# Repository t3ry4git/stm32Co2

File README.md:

# stm32Co2

A simple CO2 and environmental monitor based on the STM32F103C8 microcontroller. The firmware reads temperature and humidity from a DHT22 sensor, measures CO2 concentration using an MHZ19B module and displays values on an SSD1306 OLED screen.

## Hardware requirements

- **MCU:** STM32F103C8 ("Blue Pill" or compatible)
- **Temperature/Humidity sensor:** DHT22
- **CO2 sensor:** MHZ19B (UART interface)
- **Display:** SSD1306 I2C OLED

## Building with STM32CubeIDE

1. Open the `test.ioc` project file in STM32CubeIDE.
2. Let CubeIDE generate the project files if prompted.
3. Build the `test` target from the IDE. Default settings produce both `Debug` and `Release` outputs.
4. Flash the resulting binary to your board using the built‑in CubeIDE programmer or an external tool such as ST‑Link.

## Third‑party software

This repository includes STM32 HAL drivers from STMicroelectronics under the BSD‑3‑Clause license as found in `Drivers/STM32F1xx_HAL_Driver/LICENSE.txt`. The SSD1306 display driver and font code in `Core/Src` and `Core/Inc` are distributed under the GNU GPL version 3.

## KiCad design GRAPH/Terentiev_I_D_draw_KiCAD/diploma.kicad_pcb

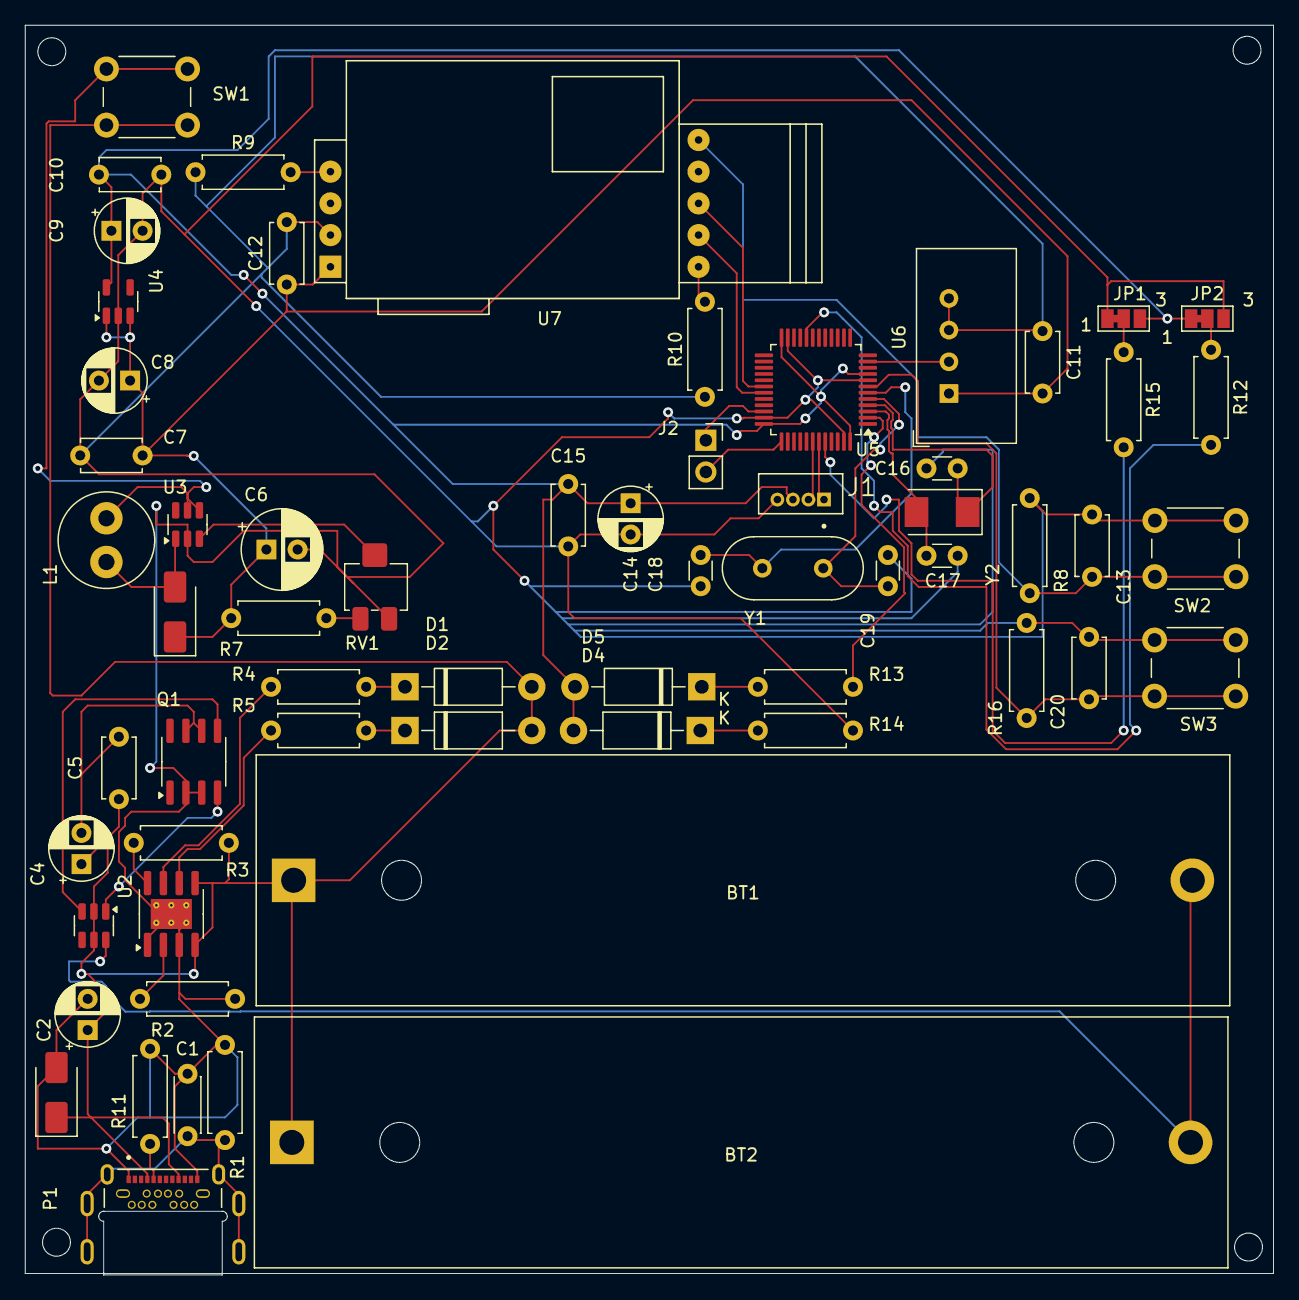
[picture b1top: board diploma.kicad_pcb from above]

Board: 2 copper layers, 100.0 x 100.0 mm, 62 parts (0 on the bottom side), 42 nets.

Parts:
BT1, BT2: 1043; BatteryHolder_MPD_BH-18650-PC2
C1: 1 nF; C_Disc_D4.3mm_W1.9mm_P5.00mm
C2, C4, C8, C9, C14: 10 uF; CP_Radial_D5.0mm_P2.50mm
C5, C7, C10, C11, C12, C13, C15, C20: 100 nF; C_Disc_D4.7mm_W2.5mm_P5.00mm
C6: 22 uF; CP_Radial_D6.3mm_P2.50mm
C16, C17: 100 pF; C_Disc_D3.0mm_W1.6mm_P2.50mm
C18, C19: 12 pF; C_Disc_D3.0mm_W1.6mm_P2.50mm
D1: RED; D_DO-41_SOD81_P10.16mm_Horizontal
D2, D4, D5: GREEN; D_DO-41_SOD81_P10.16mm_Horizontal
D3, D6: SS34; D_SMA
J1: OLED_LCD; TE_1734598-4
J2: Flash; PinSocket_1x02_P2.54mm_Vertical
JP1: Boot0; SolderJumper-3_P1.3mm_Bridged12_Pad1.0x1.5mm_NumberLabels
JP2: Boot1; SolderJumper-3_P1.3mm_Bridged12_Pad1.0x1.5mm_NumberLabels
L1: 22uH/2A; L_Radial_D7.5mm_P3.50mm_Fastron_07P
P1: USBC; usbc
Q1: FS8205A; SOIC-8_3.9x4.9mm_P1.27mm
R1: 1 M; R_Axial_DIN0207_L6.3mm_D2.5mm_P7.62mm_Horizontal
R2: 1.2k; R_Axial_DIN0207_L6.3mm_D2.5mm_P7.62mm_Horizontal
R3, R8, R16: 10 k; R_Axial_DIN0207_L6.3mm_D2.5mm_P7.62mm_Horizontal
R4, R5: 1k; R_Axial_DIN0207_L6.3mm_D2.5mm_P7.62mm_Horizontal
R7, R9, R10: 100 k; R_Axial_DIN0207_L6.3mm_D2.5mm_P7.62mm_Horizontal
R11: 5.1 k; R_Axial_DIN0207_L6.3mm_D2.5mm_P7.62mm_Horizontal
R12, R15: 100k; R_Axial_DIN0207_L6.3mm_D2.5mm_P7.62mm_Horizontal
R13, R14: 510; R_Axial_DIN0207_L6.3mm_D2.5mm_P7.62mm_Horizontal
RV1: 2.2 k; Potentiometer_Bourns_3214X_Vertical
SW1: Enable Switch; SW_PUSH_6mm
SW2: Calibrate; SW_PUSH_6mm
SW3: Reset; SW_PUSH_6mm
U1: TP4056; SOIC-8-1EP_3.9x4.9mm_P1.27mm_EP2.41x3.3mm_ThermalVias
U2: DW01A; SOT-23-6
U3: MT3608; SOT-23-6
U4: AP2112K-3.3; SOT-23-5
U5: STM32F103C8T6; LQFP-48_7x7mm_P0.5mm
U6: DHT22; ASAIR_AM2302_P2.54mm_Vertical
U7: MH-Z19B
Y1: 8MHz; Crystal_HC49-U_Vertical
Y2: 32768Hz; Crystal_SMD_Abracon_ABM3-2Pin_5.0x3.2mm

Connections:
+3.3V: C9.1, C10.1, C14.1, C15.1, D4.2 (A), D5.2 (A), J1.3, JP1.3 (B), JP2.1 (A), U4.5 (VOUT), U5.9 (VDDA), U5.24 (VDD), U5.36 (VDD), U5.48 (VDD)
+5V: C6.1, C7.1, C8.1, C11.2, C12.1, D3.1 (K), R7.1, U4.1 (VIN), U4.3 (EN), U6.1 (VDD), U7.VIN
GND: C1.2, C2.2, C6.2, C7.2, C8.2, C9.2, C10.2, C11.1, C12.2, C13.2, C14.2, C15.2, C16.1, C17.1, C18.2, C19.2, C20.2, D6.2 (A), J1.4, JP1.1 (A), JP2.3 (B), P1.A1 (GND_A), P1.A12 (GND_A), Q1.2, Q1.3, R1.2, R2.2, R8.2, R9.1, R10.1, R11.2, R14.1, R16.1, RV1.3, SW2.2, SW3.2, U1.1 (TEMP), U1.3 (GND), U1.9 (EPAD), U3.2 (GND), U4.2 (GND), U5.8 (VSSA), U5.23 (VSS), U5.35 (VSS), U5.47 (VSS), U6.3 (GND), U6.4 (GND), U7.GND
unnamed: C1.1, P1.SH1 (SHIELD), P1.SH2 (SHIELD), P1.SH3 (SHIELD), P1.SH4 (SHIELD), P1.SH5 (SHIELD), P1.SH6 (SHIELD), R1.1
unnamed: C4.2, C5.2, Q1.6, Q1.7
unnamed: C13.1, R8.1, SW2.1, U7.HD
unnamed: BT1.1, BT2.1, C2.1, C4.1, C5.1, D1.2 (A), D2.2 (A), D6.1 (K), P1.A4 (VBUS_A), P1.A9 (VBUS_A), R3.1, SW1.1 (A), U1.4 (V_{CC}), U1.5 (BAT), U2.2 (CS), U2.5 (VCC)
unnamed: D1.1 (K), R4.1
unnamed: D2.1 (K), R5.2
unnamed: D3.2 (A), L1.2, U3.1 (SW)
unnamed: D4.1 (K), R14.2
unnamed: D5.1 (K), R13.2
unnamed: J1.1, U5.43 (PB7)
unnamed: J1.2, U5.42 (PB6)
unnamed: J2.1, U5.34 (PA13)
unnamed: J2.2, U5.37 (PA14)
unnamed: JP1.2 (C), R15.1
unnamed: JP2.2 (C), R12.1
unnamed: P1.A5 (CC1), R11.1
unnamed: R7.2, RV1.1
unnamed: R9.2, U7.PWM
unnamed: R10.2, U7.VO
unnamed: L1.1, SW1.2 (B), U3.4 (EN), U3.5 (IN)
unnamed: R3.2, U1.8 (CE)
unnamed: R2.1, U1.2 (PROG)
unnamed: R4.2, U1.7 (~CHRG)
unnamed: R5.1, U1.6 (~STDBY)
unnamed: BT1.2, BT2.2, U2.6 (GND)
unnamed: Q1.5, U2.3 (OC)
unnamed: Q1.4, U2.1 (OD)
unnamed: RV1.2, U3.3 (FB)
unnamed: R15.2, U5.44 (BOOT0)
unnamed: C20.1, R16.2, SW3.1, U5.7 (NRST)
unnamed: U5.11 (PA1), U6.2 (SDA)
unnamed: U5.30 (PA9), U7.TX
unnamed: U5.31 (PA10), U7.RX
unnamed: R12.2, U5.20 (PB2)
unnamed: R13.1, U5.2 (PC13)
unnamed: C17.2, U5.3 (PC14), Y2.2
unnamed: C16.2, U5.4 (PC15), Y2.1
unnamed: C19.1, U5.5 (PD0), Y1.2
unnamed: C18.1, U5.6 (PD1), Y1.1

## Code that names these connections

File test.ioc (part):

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Mcu.Name=STM32F103C(8-B)Tx
Mcu.Package=LQFP48
Mcu.UserName=STM32F103C8Tx
PA10.Mode=Asynchronous
PA10.Signal=USART1_RX
PA13.Mode=Serial_Wire
PA13.Signal=SYS_JTMS-SWDIO
PA14.Mode=Serial_Wire
PA14.Signal=SYS_JTCK-SWCLK
PA9.Mode=Asynchronous
PA9.Signal=USART1_TX
PB6.Mode=I2C
PB6.Signal=I2C1_SCL
PB7.Mode=I2C
PB7.Signal=I2C1_SDA
PC13-TAMPER-RTC.GPIOParameters=GPIO_Label
PC13-TAMPER-RTC.GPIO_Label=boardLED
PC13-TAMPER-RTC.Signal=GPIO_Output
PD0-OSC_IN.Mode=HSE-External-Oscillator
PD0-OSC_IN.Signal=RCC_OSC_IN
PD1-OSC_OUT.Mode=HSE-External-Oscillator
PD1-OSC_OUT.Signal=RCC_OSC_OUT
RCC.SYSCLKFreq_VALUE=72000000
RCC.SYSCLKSource=RCC_SYSCLKSOURCE_PLLCLK
board=custom

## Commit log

2025-06-03 Limit I2C multi-write count
2025-06-03 Add README details and license
2025-06-03 Fix checksum variable type
2025-06-03 Add gitignore and remove generated files
2025-07-28 files
